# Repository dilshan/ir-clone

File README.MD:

IR Remote Control Clone Utility
===============================

IR Clone is an open-source infrared remote control signal analysis and generating tool. This utility can clone IR signals, examine the IR remote control signals, and modify or create new IR signals. 

This project consists of both hardware and software utilities. The hardware module contains an 8-bit MCU, 32Kbit EEPROM, IR receiver, and transmitter.

The software application provides options to decode captured data and generate new IR signals.

IR Clone is an [OSHW certified](https://certification.oshwa.org/lk000011.html) open-source project. All the schematics, PCB design files, firmware source codes, and application source codes are available in this repository.

The complete [documentation](https://github.com/dilshan/ir-clone/wiki) of this project is available in the [wiki](https://github.com/dilshan/ir-clone/wiki) section of this repository. The PCB Gerber files and compiled binaries are also available in the [release](https://github.com/dilshan/ir-clone/releases) section of this repository.

All the content of this project are distributed under the terms of the following license:

- Hardware License: [CERN-OHL-W 2.0](https://ohwr.org/cern_ohl_w_v2.txt)
- Software License: [MIT](https://github.com/dilshan/ir-clone/blob/main/LICENSE)
- [Documentation](https://github.com/dilshan/ir-clone/wiki) License: [CC BY 4.0](https://creativecommons.org/licenses/by/4.0/)

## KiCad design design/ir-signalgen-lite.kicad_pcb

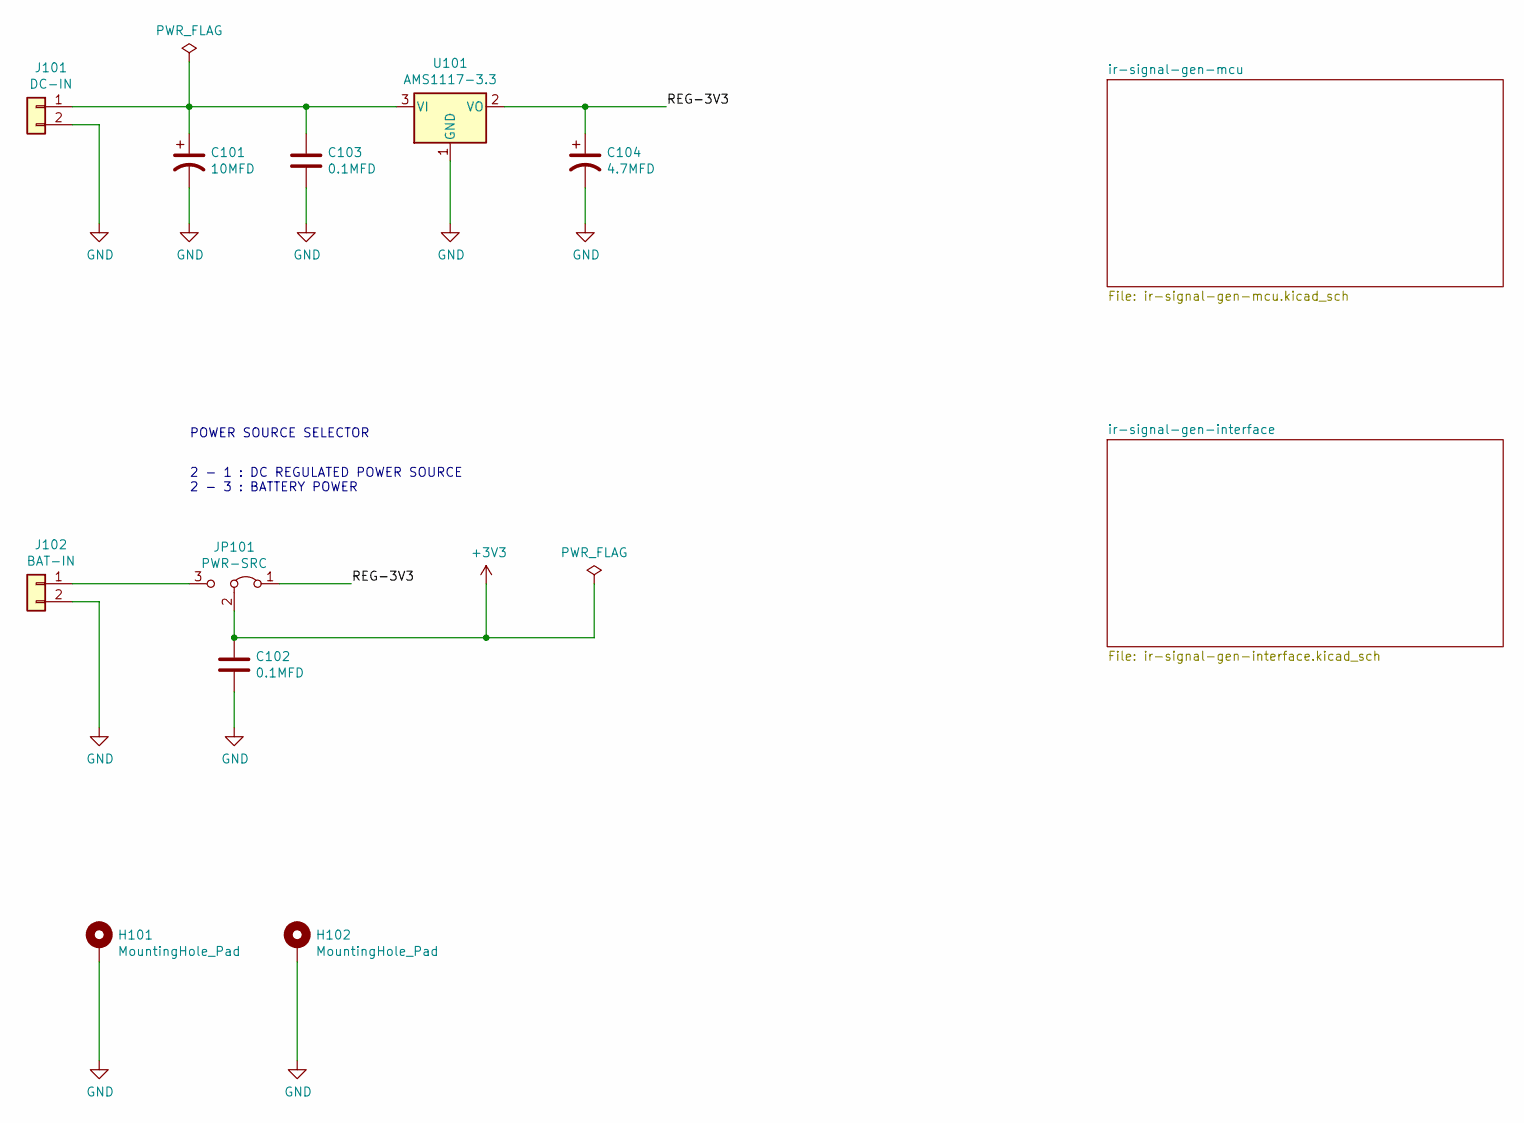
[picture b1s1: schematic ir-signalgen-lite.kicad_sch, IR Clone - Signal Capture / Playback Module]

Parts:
C101: 10MFD; CP_Radial_D5.0mm_P2.50mm
C102, C103: 0.1MFD; C_0805_2012Metric_Pad1.18x1.45mm_HandSolder
C104: 4.7MFD; CP_Radial_D5.0mm_P2.50mm
H101, H102: MountingHole_Pad; MountingHole_3.2mm_M3_Pad
J101: DC-IN; PhoenixContact_MCV_1,5_2-G-3.5_1x02_P3.50mm_Vertical
J102: BAT-IN; PinHeader_1x02_P2.54mm_Vertical
JP101: PWR-SRC; PinHeader_1x03_P2.54mm_Vertical
U101: AMS1117-3.3; SOT-223-3_TabPin2

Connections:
+3V3: C102.1, JP101.2 (C); also elsewhere on the board
/REG-3V3: C104.1, JP101.1 (A), U101.2 (VO)
GND: C101.2, C102.2, C103.2, C104.2, H101.1, H102.1, J101.2, J102.2, U101.1 (GND); also elsewhere on the board
unnamed: C101.1, C103.1, J101.1, U101.3 (VI)
unnamed: J102.1, JP101.3 (B)

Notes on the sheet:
POWER SOURCE SELECTOR
2 - 1 : DC REGULATED POWER SOURCE 2 - 3 : BATTERY POWER

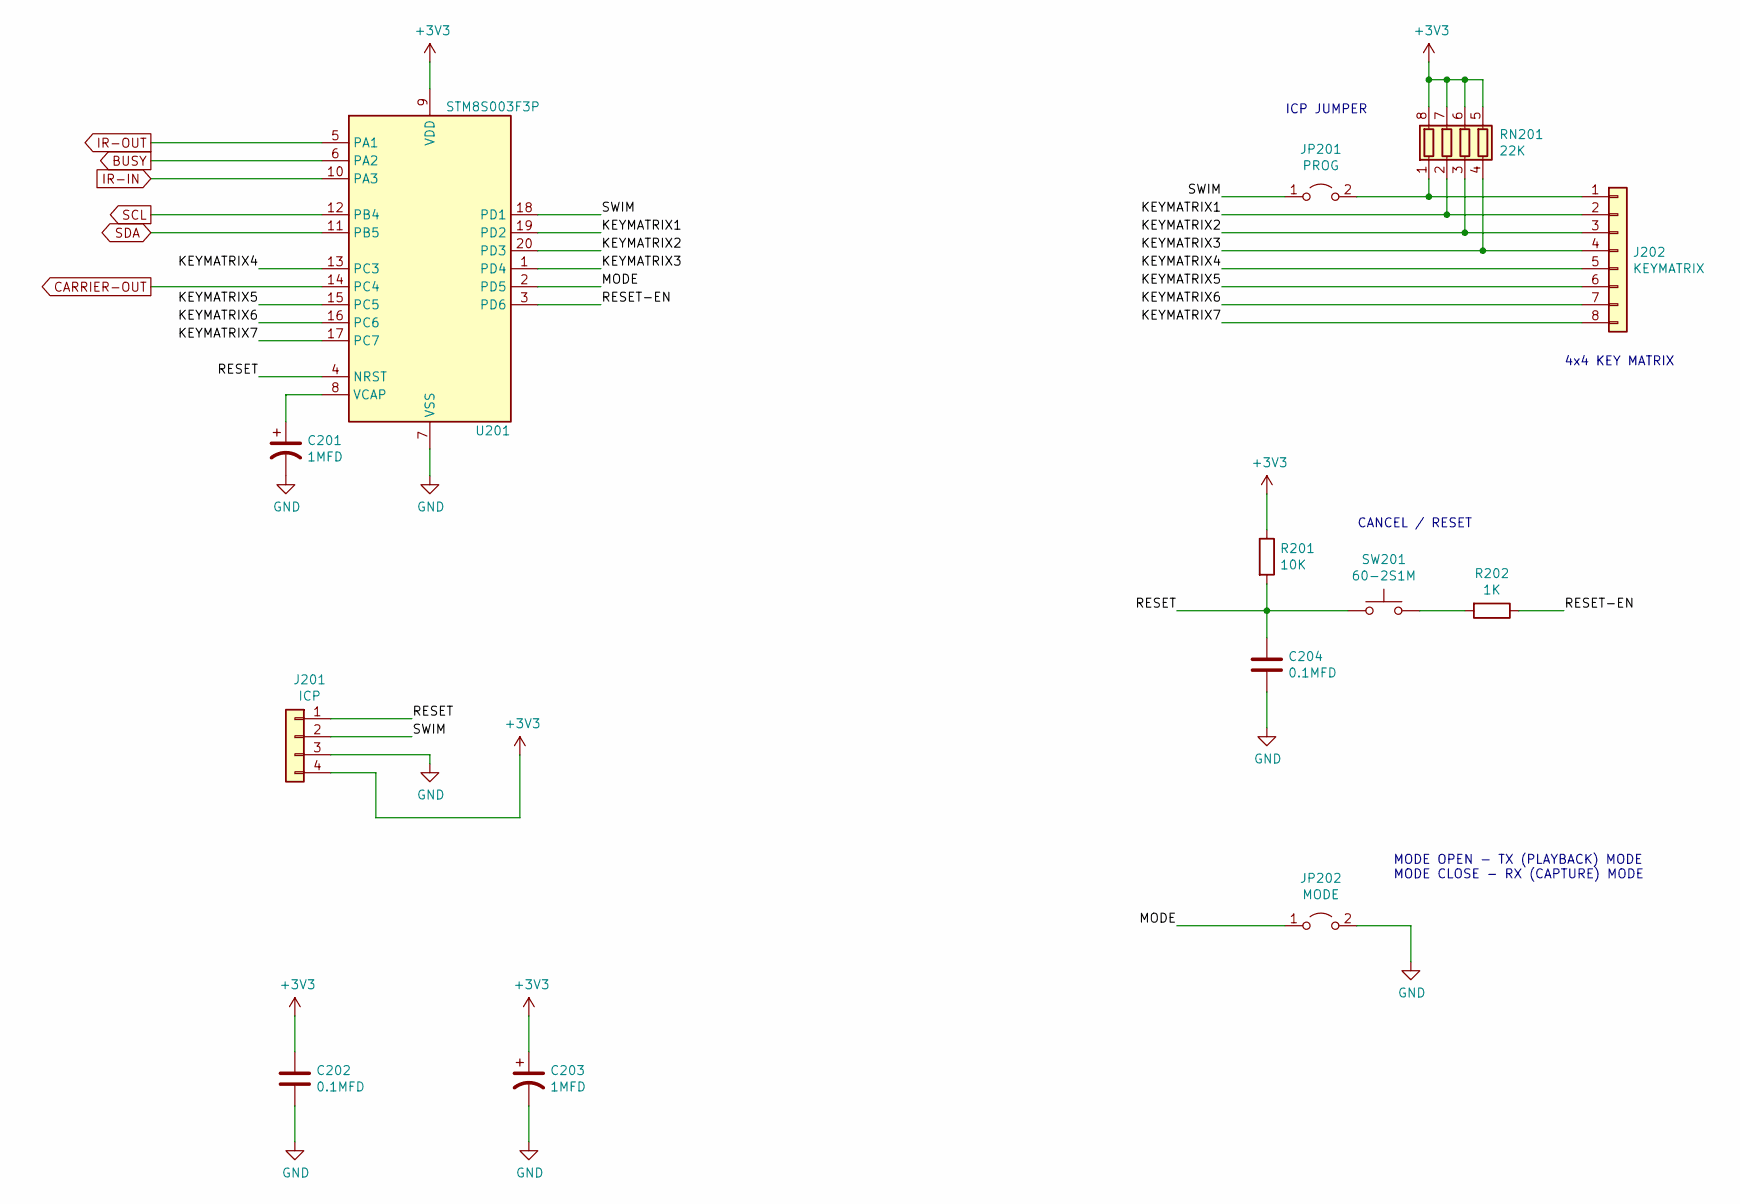
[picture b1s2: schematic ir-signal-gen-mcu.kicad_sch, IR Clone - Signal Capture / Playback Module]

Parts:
C201: 1MFD; C_0805_2012Metric_Pad1.18x1.45mm_HandSolder
C202, C204: 0.1MFD; C_0805_2012Metric_Pad1.18x1.45mm_HandSolder
C203: 1MFD; CP_Radial_D5.0mm_P2.50mm
J201: ICP; pogo-2.54mmx4
J202: KEYMATRIX; PinHeader_1x08_P2.54mm_Vertical
JP201: PROG; SolderJumper-2_P1.3mm_Bridged_Pad1.0x1.5mm
JP202: MODE; PinHeader_1x02_P2.54mm_Vertical
R201: 10K; R_0805_2012Metric_Pad1.20x1.40mm_HandSolder
R202: 1K; R_0805_2012Metric_Pad1.20x1.40mm_HandSolder
RN201: 22K; R_Array_Convex_4x0603
SW201: 60-2S1M; SW_PUSH_6mm
U201: STM8S003F3P; TSSOP-20_4.4x6.5mm_P0.65mm

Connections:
+3V3: C202.1, C203.1, J201.4, R201.1, RN201.5 (R4.2), RN201.6 (R3.2), RN201.7 (R2.2), RN201.8 (R1.2), U201.9 (VDD); also elsewhere on the board
/ir-signal-gen-mcu/KEYMATRIX1: J202.2, RN201.2 (R2.1), U201.19 (PD2)
/ir-signal-gen-mcu/KEYMATRIX2: J202.3, RN201.3 (R3.1), U201.20 (PD3)
/ir-signal-gen-mcu/KEYMATRIX3: J202.4, RN201.4 (R4.1), U201.1 (PD4)
/ir-signal-gen-mcu/KEYMATRIX4: J202.5, U201.13 (PC3)
/ir-signal-gen-mcu/KEYMATRIX5: J202.6, U201.15 (PC5)
/ir-signal-gen-mcu/KEYMATRIX6: J202.7, U201.16 (PC6)
/ir-signal-gen-mcu/KEYMATRIX7: J202.8, U201.17 (PC7)
/ir-signal-gen-mcu/MODE: JP202.1 (A), U201.2 (PD5)
/ir-signal-gen-mcu/RESET: C204.1, J201.1, R201.2, SW201.1, U201.4 (NRST)
/ir-signal-gen-mcu/RESET-EN: R202.1, U201.3 (PD6)
/ir-signal-gen-mcu/SWIM: J201.2, JP201.1 (A), U201.18 (PD1)
BUSY: U201.6 (PA2); also elsewhere on the board
CARRIER-OUT: U201.14 (PC4); also elsewhere on the board
GND: C201.2, C202.2, C203.2, C204.2, J201.3, JP202.2 (B), U201.7 (VSS); also elsewhere on the board
IR-IN: U201.10 (PA3); also elsewhere on the board
IR-OUT: U201.5 (PA1); also elsewhere on the board
unnamed: C201.1, U201.8 (VCAP)
unnamed: J202.1, JP201.2 (B), RN201.1 (R1.1)
unnamed: R202.2, SW201.2
SCL: U201.12 (PB4); also elsewhere on the board
SDA: U201.11 (PB5); also elsewhere on the board

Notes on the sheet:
ICP JUMPER
CANCEL / RESET
MODE OPEN - TX (PLAYBACK) MODE MODE CLOSE - RX (CAPTURE) MODE
4x4 KEY MATRIX

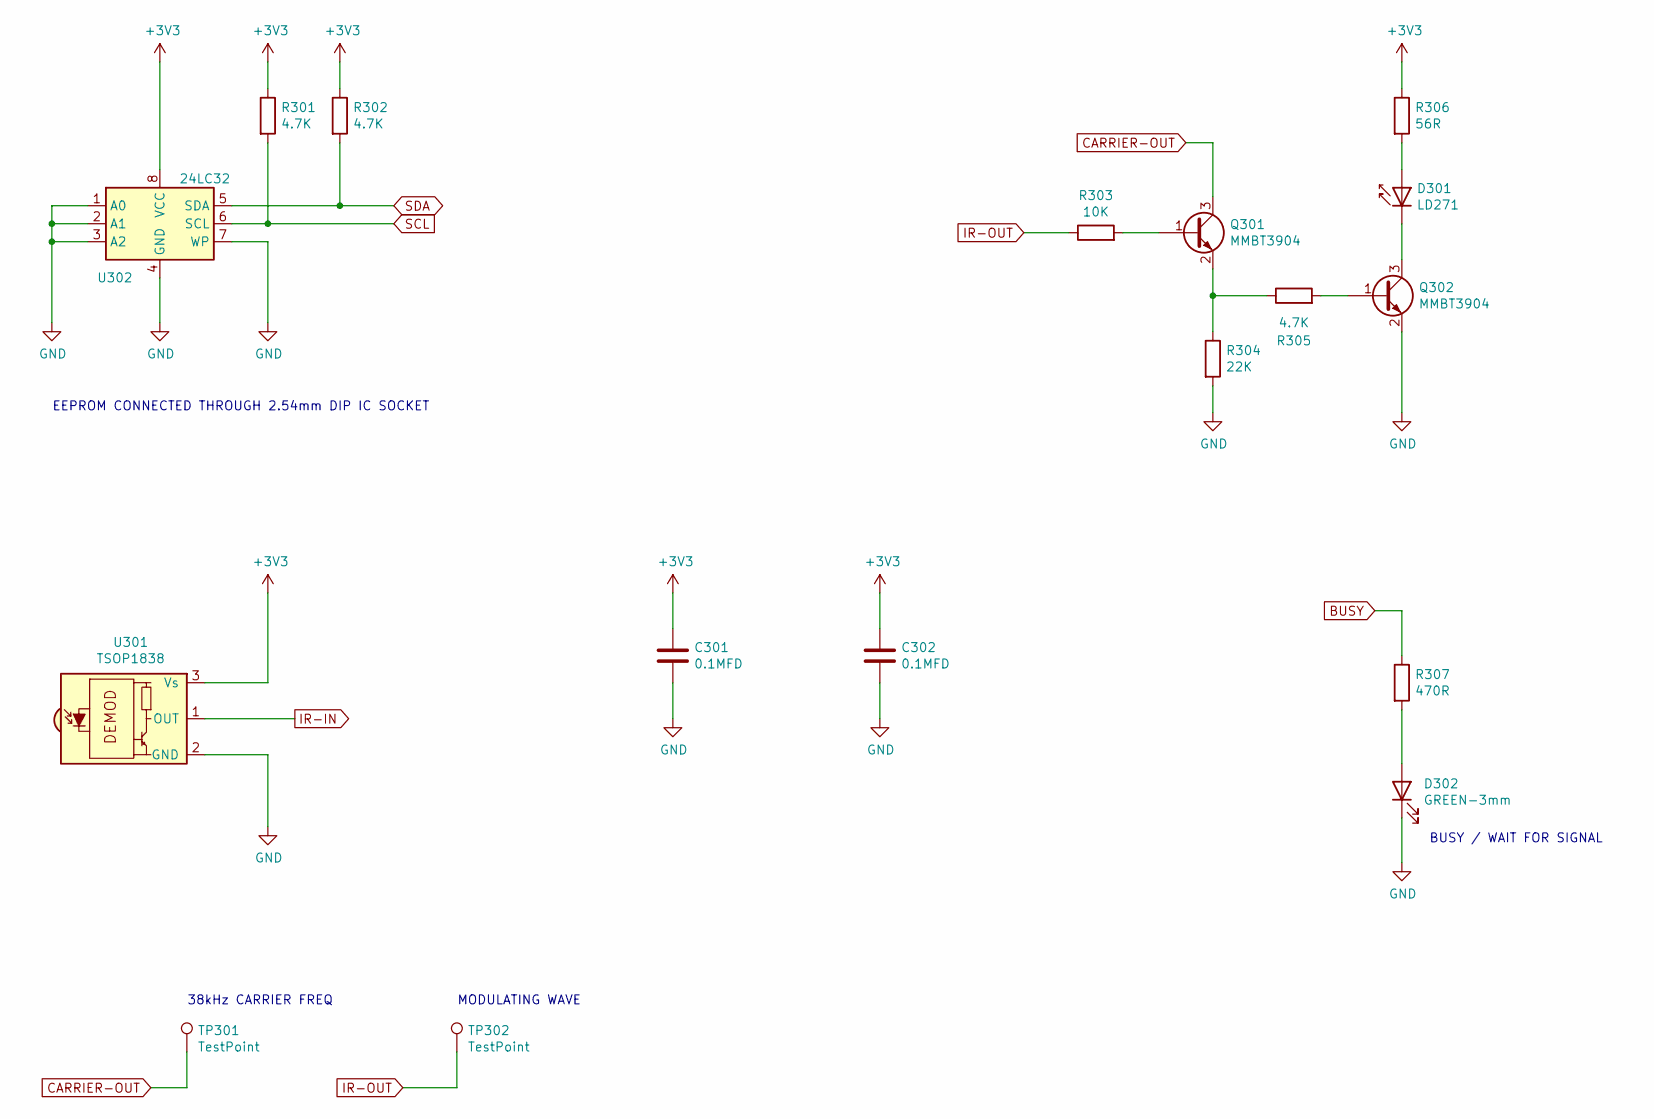
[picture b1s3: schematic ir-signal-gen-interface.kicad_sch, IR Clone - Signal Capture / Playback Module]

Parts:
C301, C302: 0.1MFD; C_0805_2012Metric_Pad1.18x1.45mm_HandSolder
D301: LD271; LED_D5.0mm_Horizontal_O1.27mm_Z3.0mm
D302: GREEN-3mm; LED_D3.0mm
Q301, Q302: MMBT3904; SOT-23
R301, R302, R305: 4.7K; R_0805_2012Metric_Pad1.20x1.40mm_HandSolder
R303: 10K; R_0805_2012Metric_Pad1.20x1.40mm_HandSolder
R304: 22K; R_0805_2012Metric_Pad1.20x1.40mm_HandSolder
R306: 56R; R_Axial_DIN0207_L6.3mm_D2.5mm_P10.16mm_Horizontal
R307: 470R; R_0805_2012Metric_Pad1.20x1.40mm_HandSolder
TP301, TP302: TestPoint; TestPoint_Pad_D1.0mm
U301: TSOP1838; Vishay_MOLD-3Pin
U302: 24LC32; DIP-8_W7.62mm_Socket_LongPads

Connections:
+3V3: C301.1, C302.1, R301.1, R302.1, R306.1, U301.3 (Vs), U302.8 (VCC); also elsewhere on the board
BUSY: R307.1; also elsewhere on the board
CARRIER-OUT: Q301.3 (C), TP301.1; also elsewhere on the board
GND: C301.2, C302.2, D302.1 (K), Q302.2 (E), R304.2, U301.2 (GND), U302.1 (A0), U302.2 (A1), U302.3 (A2), U302.4 (GND), U302.7 (WP); also elsewhere on the board
IR-IN: U301.1 (OUT); also elsewhere on the board
IR-OUT: R303.1, TP302.1; also elsewhere on the board
unnamed: D301.1 (K), Q302.3 (C)
unnamed: D301.2 (A), R306.2
unnamed: D302.2 (A), R307.2
unnamed: Q301.1 (B), R303.2
unnamed: Q301.2 (E), R304.1, R305.1
unnamed: Q302.1 (B), R305.2
SCL: R301.2, U302.6 (SCL); also elsewhere on the board
SDA: R302.2, U302.5 (SDA); also elsewhere on the board

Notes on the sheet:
MODULATING WAVE
38kHz CARRIER FREQ
BUSY / WAIT FOR SIGNAL
EEPROM CONNECTED THROUGH 2.54mm DIP IC SOCKET

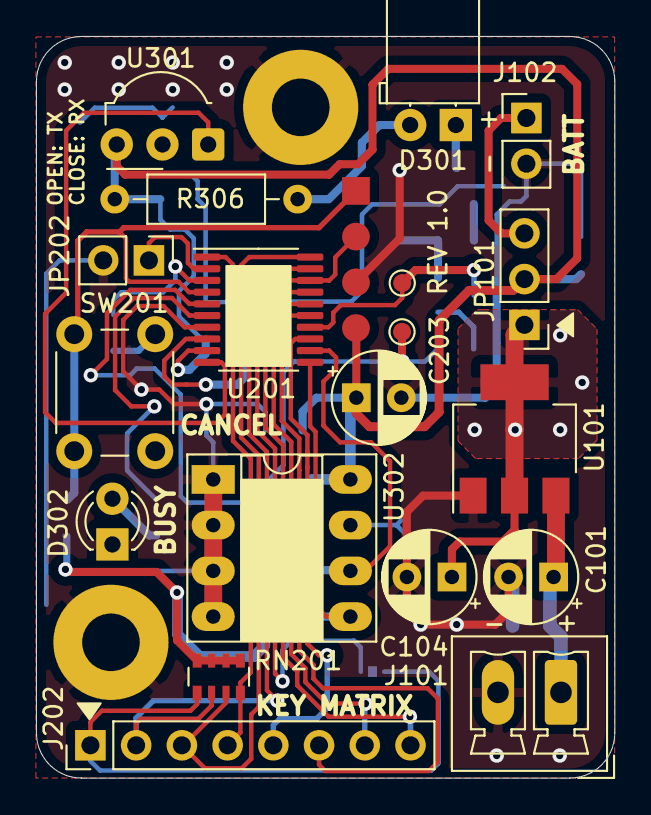
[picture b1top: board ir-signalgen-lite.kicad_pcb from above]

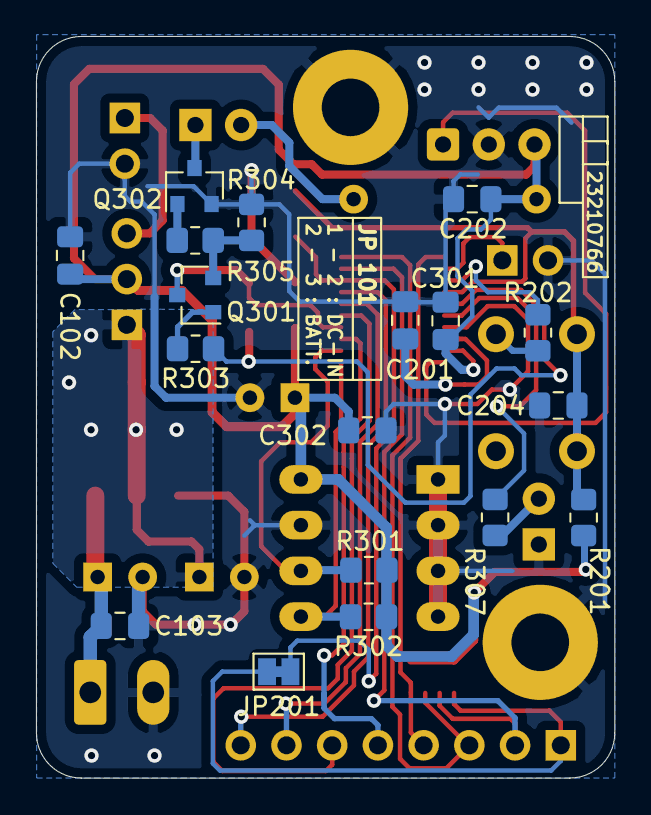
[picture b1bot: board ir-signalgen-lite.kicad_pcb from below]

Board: 2 copper layers, 32.1 x 41.2 mm, 40 parts (18 on the bottom side), 31 nets.

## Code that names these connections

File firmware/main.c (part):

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    // Waiting for switching to new clock configuration.
    while(CLK_SWCR & 0x01);

    // PA1[OUT] : IR LED drive.
    // PA2[OUT] : Capture / Busy status LED.
    // PA3[IN]  : TSSOP1838 IR photo module input.
    PA_DDR = 0xF7;
    PA_CR1 = 0xFF;
    PA_CR2 = 0x00;
    PA_ODR = 0x00;

    // PD1..PD4 [IN] : Keyboard input.
    // PD5[IN]  : Capture / Transmit mode selector.
    // PD6[OUT] : Reset control pin.
    PD_DDR = 0xC1;
    PD_CR1 = 0x60;
    PD_CR2 = 0x00;
    PD_ODR = 0x40;

    // PC3, PC4..PC7 [OUT] : Keyboard scan data.
    PC_DDR = 0xE8;
    PC_CR1 = 0xE8;
    PC_CR2 = 0x00;
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
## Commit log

2022-02-12 Add initial version of firmware and IR clone utility.
2022-02-12 Add initial version of schematic and PCB design files.
2022-02-15 Create initial version of README.MD file.
2022-02-15 Create initial version of CI workflow.
2022-02-15 Update title of the README.MD file.
2022-02-15 Add Python script to plot waveform from the EEPROM dump.
2022-02-16 Update readme.md file with license information.
2022-02-16 Add Fritzing design files and test setup schematic.
2022-02-16 Update test setup with description.
2022-02-16 Add test setup with 3V battery power.
2022-02-16 Update Fritzing layouts with JP101 positions.
2022-02-16 Add initial version of PCB mounting layout.
2022-02-16 Add link to documentation/wiki.
2022-02-16 Add YouTube video thumbnail :camera:
2022-02-16 Add video link to the README.MD file.
2022-02-16 Add link to the release section.
2022-02-25 Add OSHW mark and fact images.
2022-02-25 Add OSHW certification details and links to the REAME.MD file.
2022-02-25 Fix minor text issues in README.MD file

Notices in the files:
firmware/main.c:
Copyright (c) 2022 Dilshan R Jayakody
